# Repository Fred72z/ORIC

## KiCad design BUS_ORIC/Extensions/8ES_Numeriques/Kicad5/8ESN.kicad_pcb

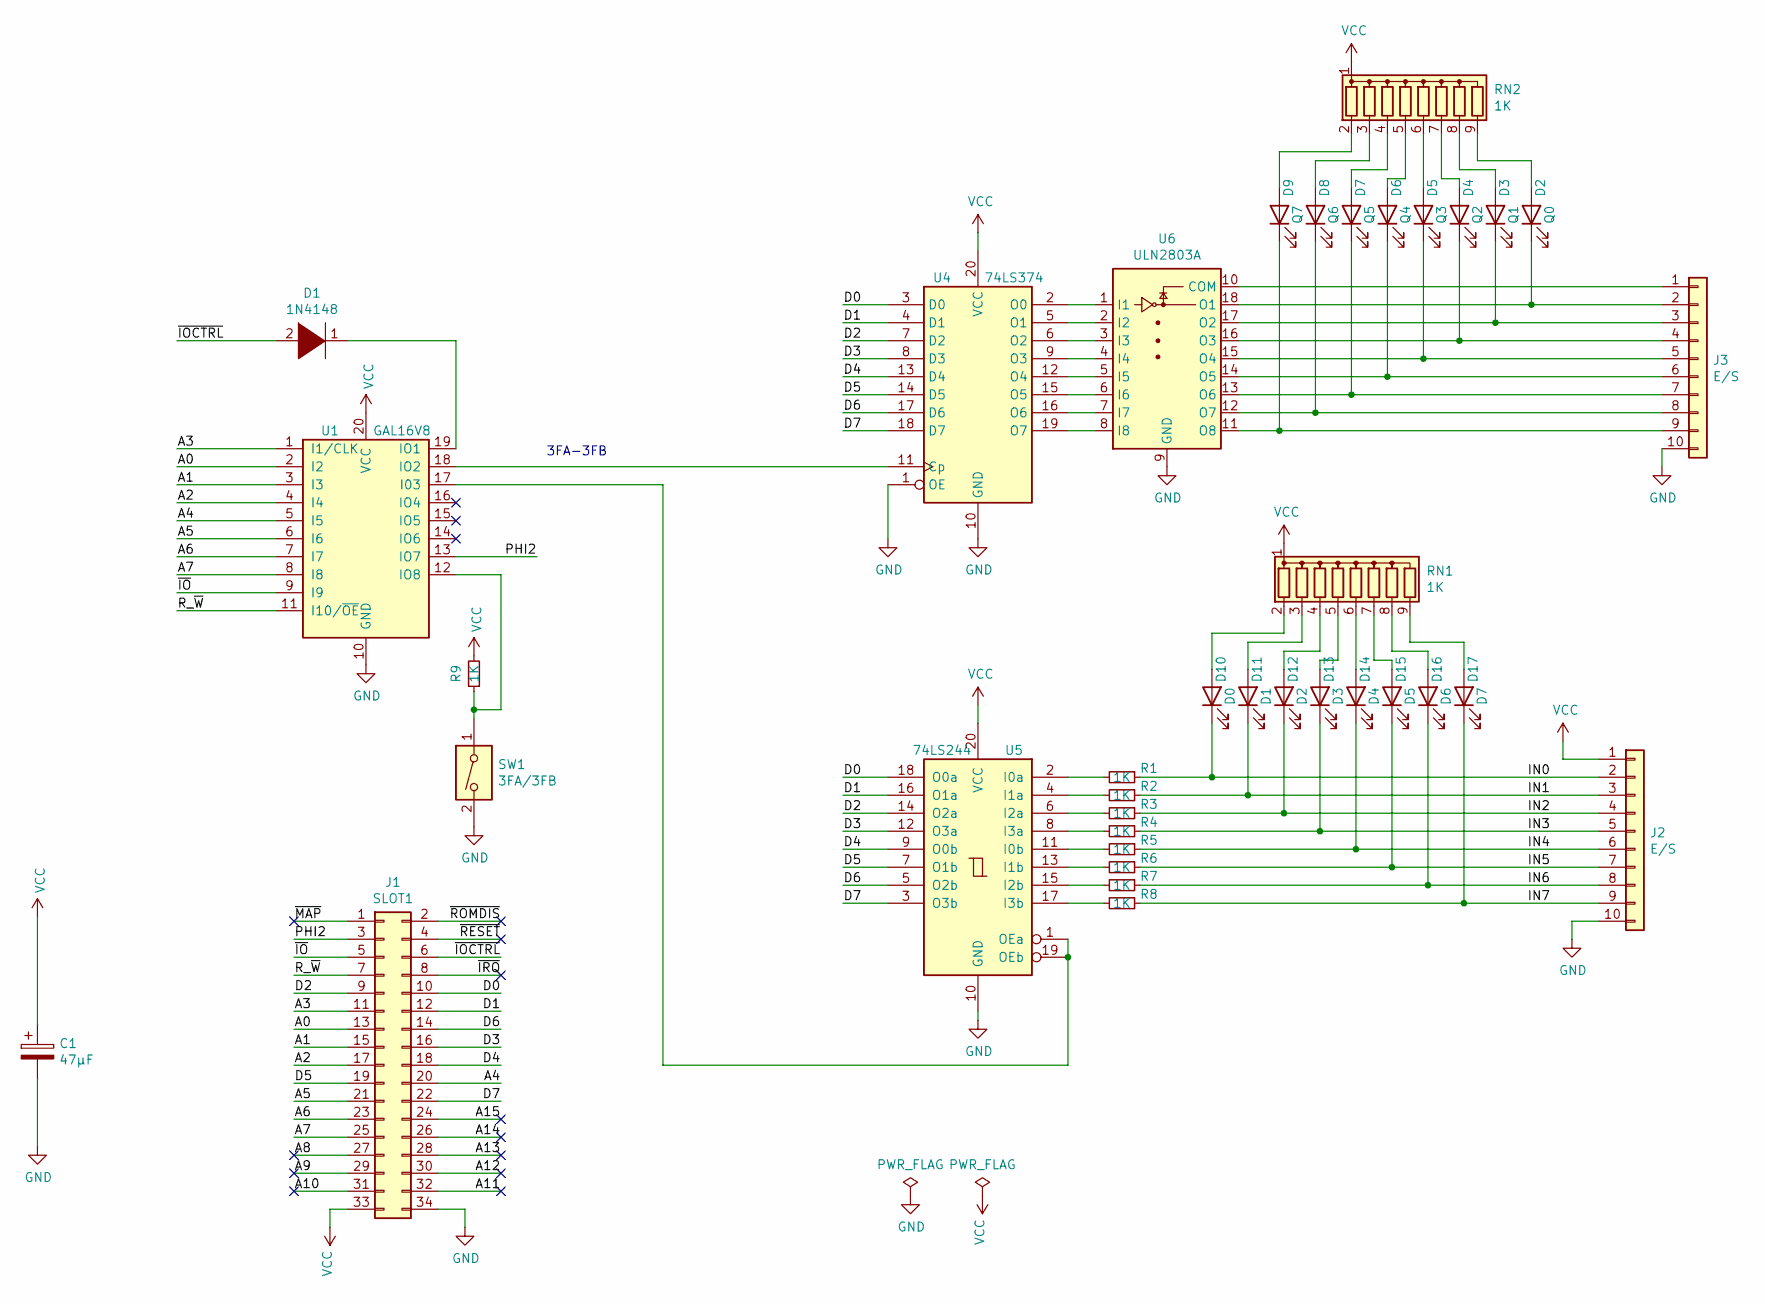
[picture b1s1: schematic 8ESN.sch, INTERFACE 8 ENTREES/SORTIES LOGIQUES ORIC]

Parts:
C1: 47µF; CP_Radial_D5.0mm_P2.00mm
D1: 1N4148; D_DO-35_SOD27_P7.62mm_Horizontal
D2: Q0; LED_0805_2012Metric
D3: Q1; LED_0805_2012Metric
D4: Q2; LED_0805_2012Metric
D5: Q3; LED_0805_2012Metric
D6: Q4; LED_0805_2012Metric
D7: Q5; LED_0805_2012Metric
D8: Q6; LED_0805_2012Metric
D9: Q7; LED_0805_2012Metric
D10: D0; LED_0805_2012Metric
D11: D1; LED_0805_2012Metric
D12: D2; LED_0805_2012Metric
D13: D3; LED_0805_2012Metric
D14: D4; LED_0805_2012Metric
D15: D5; LED_0805_2012Metric
D16: D6; LED_0805_2012Metric
D17: D7; LED_0805_2012Metric
J1: SLOT1; IDC-Header_2x17_P2.54mm_Horizontal
J2, J3: E/S; PinHeader_1x10_P2.54mm_Horizontal
R1, R2, R3, R4, R5, R6, R7, R8: 1K; R_Axial_DIN0204_L3.6mm_D1.6mm_P2.54mm_Vertical
R9: 1K; R_Axial_DIN0204_L3.6mm_D1.6mm_P7.62mm_Horizontal
RN1, RN2: 1K; R_Array_SIP9
SW1: 3FA/3FB; SW_DIP_SPSTx01_Slide_6.7x4.1mm_W7.62mm_P2.54mm_LowProfile
U1: GAL16V8; DIP-20_W7.62mm_LongPads
U4: 74LS374; DIP-20_W7.62mm_LongPads
U5: 74LS244; DIP-20_W7.62mm_LongPads
U6: ULN2803A; DIP-18_W7.62mm_LongPads

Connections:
/A0: J1.13, U1.2 (I2)
/A1: J1.15, U1.3 (I3)
/A2: J1.17, U1.4 (I4)
/A3: J1.11, U1.1 (I1/CLK)
/A4: J1.20, U1.5 (I5)
/A5: J1.21, U1.6 (I6)
/A6: J1.23, U1.7 (I7)
/A7: J1.25, U1.8 (I8)
/A8: J1.27
/A9: J1.29
/A10: J1.31
/A11: J1.32
/A12: J1.30
/A13: J1.28
/A14: J1.26
/A15: J1.24
/D0: J1.10, U4.3 (D0), U5.18 (O0a)
/D1: J1.12, U4.4 (D1), U5.16 (O1a)
/D2: J1.9, U4.7 (D2), U5.14 (O2a)
/D3: J1.16, U4.8 (D3), U5.12 (O3a)
/D4: J1.18, U4.13 (D4), U5.9 (O0b)
/D5: J1.19, U4.14 (D5), U5.7 (O1b)
/D6: J1.14, U4.17 (D6), U5.5 (O2b)
/D7: J1.22, U4.18 (D7), U5.3 (O3b)
/IN0: D10.1 (K), J2.2, R1.1
/IN1: D11.1 (K), J2.3, R2.1
/IN2: D12.1 (K), J2.4, R3.1
/IN3: D13.1 (K), J2.5, R4.1
/IN4: D14.1 (K), J2.6, R5.1
/IN5: D15.1 (K), J2.7, R6.1
/IN6: D16.1 (K), J2.8, R7.1
/IN7: D17.1 (K), J2.9, R8.1
/PHI2: J1.3, U1.13 (IO7)
/R_~W: J1.7, U1.11 (I10/~OE~)
/~IO: J1.5, U1.9 (I9)
/~IOCTRL: D1.2 (A), J1.6
/~IRQ: J1.8
/~MAP: J1.1
/~RESET: J1.4
/~ROMDIS: J1.2
GND: C1.2, J1.34, J2.10, J3.10, SW1.2, U1.10 (GND), U4.1 (OE), U4.10 (GND), U5.10 (GND), U6.9 (GND)
unnamed: D1.1 (K), U1.19 (IO1)
unnamed: D2.1 (K), J3.2, U6.18 (O1)
unnamed: D2.2 (A), RN2.9 (R8)
unnamed: D3.1 (K), J3.3, U6.17 (O2)
unnamed: D3.2 (A), RN2.8 (R7)
unnamed: D4.1 (K), J3.4, U6.16 (O3)
unnamed: D4.2 (A), RN2.7 (R6)
unnamed: D5.1 (K), J3.5, U6.15 (O4)
unnamed: D5.2 (A), RN2.6 (R5)
unnamed: D6.1 (K), J3.6, U6.14 (O5)
unnamed: D6.2 (A), RN2.5 (R4)
unnamed: D7.1 (K), J3.7, U6.13 (O6)
unnamed: D7.2 (A), RN2.4 (R3)
unnamed: D8.1 (K), J3.8, U6.12 (O7)
unnamed: D8.2 (A), RN2.3 (R2)
unnamed: D9.1 (K), J3.9, U6.11 (O8)
unnamed: D9.2 (A), RN2.2 (R1)
unnamed: D10.2 (A), RN1.2 (R1)
unnamed: D11.2 (A), RN1.3 (R2)
unnamed: D12.2 (A), RN1.4 (R3)
unnamed: D13.2 (A), RN1.5 (R4)
unnamed: D14.2 (A), RN1.6 (R5)
unnamed: D15.2 (A), RN1.7 (R6)
unnamed: D16.2 (A), RN1.8 (R7)
unnamed: D17.2 (A), RN1.9 (R8)
unnamed: J3.1, U6.10 (COM)
unnamed: R1.2, U5.2 (I0a)
unnamed: R2.2, U5.4 (I1a)
unnamed: R3.2, U5.6 (I2a)
unnamed: R4.2, U5.8 (I3a)
unnamed: R5.2, U5.11 (I0b)
unnamed: R6.2, U5.13 (I1b)
unnamed: R7.2, U5.15 (I2b)
unnamed: R8.2, U5.17 (I3b)
unnamed: R9.1, SW1.1, U1.12 (IO8)
unnamed: U1.17 (I03), U5.1 (OEa), U5.19 (OEb)
unnamed: U1.18 (IO2), U4.11 (Cp)
unnamed: U4.2 (O0), U6.1 (I1)
unnamed: U4.5 (O1), U6.2 (I2)
unnamed: U4.6 (O2), U6.3 (I3)
unnamed: U4.9 (O3), U6.4 (I4)
unnamed: U4.12 (O4), U6.5 (I5)
unnamed: U4.15 (O5), U6.6 (I6)
unnamed: U4.16 (O6), U6.7 (I7)
unnamed: U4.19 (O7), U6.8 (I8)
VCC: C1.1, J1.33, J2.1, R9.2, RN1.1 (common), RN2.1 (common), U1.20 (VCC), U4.20 (VCC), U5.20 (VCC)

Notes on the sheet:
3FA-3FB

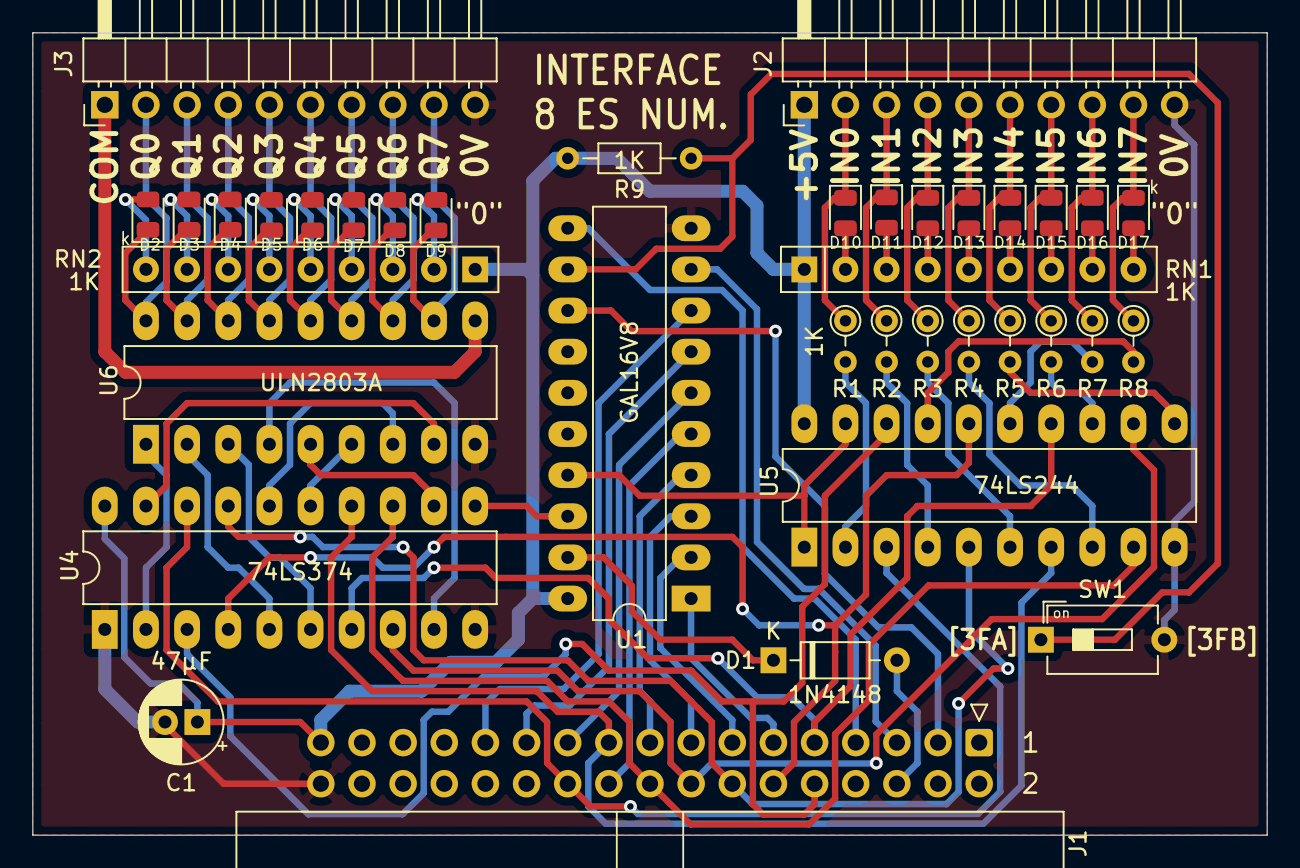
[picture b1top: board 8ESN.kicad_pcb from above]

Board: 2 copper layers, 76.2 x 49.5 mm, 37 parts (0 on the bottom side), 75 nets.

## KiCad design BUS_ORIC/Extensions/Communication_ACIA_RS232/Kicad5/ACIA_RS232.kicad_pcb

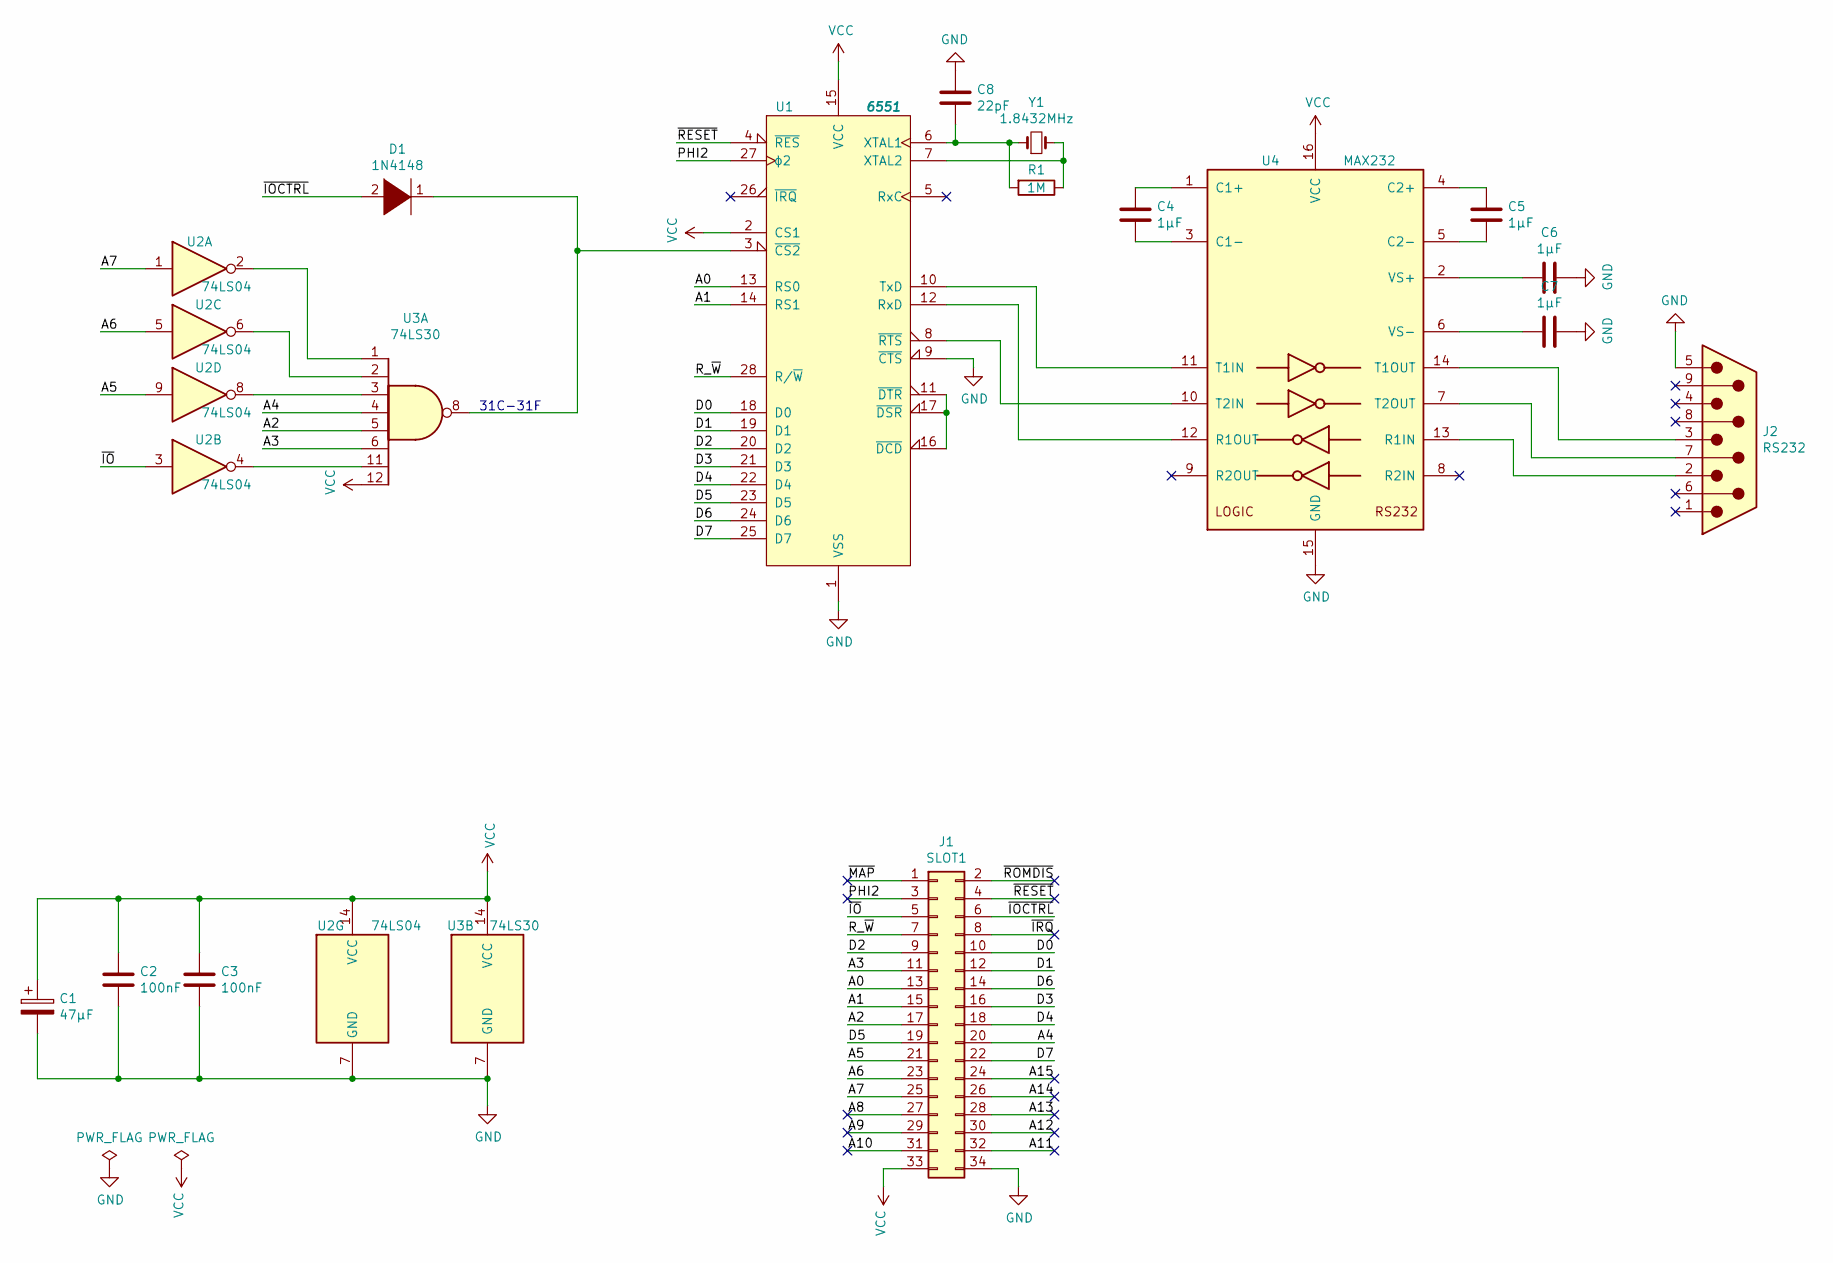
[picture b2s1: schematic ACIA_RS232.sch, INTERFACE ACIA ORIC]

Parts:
C1: 47µF; CP_Radial_D5.0mm_P2.00mm
C2, C3: 100nF; C_Rect_L7.0mm_W2.0mm_P5.00mm
C4, C5, C6, C7: 1µF; CP_Radial_D5.0mm_P2.00mm
C8: 22pF; C_Disc_D3.4mm_W2.1mm_P2.50mm
D1: 1N4148; D_DO-35_SOD27_P7.62mm_Horizontal
J1: SLOT1; IDC-Header_2x17_P2.54mm_Horizontal
J2: RS232; DSUB-9_Male_Horizontal_P2.77x2.84mm
R1: 1M; R_Axial_DIN0207_L6.3mm_D2.5mm_P10.16mm_Horizontal
U1: 6551; DIP-28_W15.24mm_LongPads
U2: 74LS04; DIP-14_W7.62mm_LongPads
U3: 74LS30; DIP-14_W7.62mm_LongPads
U4: MAX232; DIP-16_W7.62mm_LongPads
Y1: 1.8432MHz; Crystal_HC49-U_Horizontal

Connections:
/A0: J1.13, U1.13 (RS0)
/A1: J1.15, U1.14 (RS1)
/A2: J1.17, U3.5
/A3: J1.11, U3.6
/A4: J1.20, U3.4
/A5: J1.21, U2.9
/A6: J1.23, U2.5
/A7: J1.25, U2.1
/A8: J1.27
/A9: J1.29
/A10: J1.31
/A11: J1.32
/A12: J1.30
/A13: J1.28
/A14: J1.26
/A15: J1.24
/D0: J1.10, U1.18 (D0)
/D1: J1.12, U1.19 (D1)
/D2: J1.9, U1.20 (D2)
/D3: J1.16, U1.21 (D3)
/D4: J1.18, U1.22 (D4)
/D5: J1.19, U1.23 (D5)
/D6: J1.14, U1.24 (D6)
/D7: J1.22, U1.25 (D7)
/PHI2: J1.3, U1.27 (ϕ2)
/R_~W: J1.7, U1.28 (R/~W)
/~IO: J1.5, U2.3
/~IOCTRL: D1.2 (A), J1.6
/~IRQ: J1.8
/~MAP: J1.1
/~RESET: J1.4, U1.4 (~RES)
/~ROMDIS: J1.2
GND: C1.2, C2.1, C3.1, C6.1, C7.1, C8.1, J1.34, J2.5, U1.1 (VSS), U1.9 (~CTS), U2.7 (GND), U3.7 (GND), U4.15 (GND)
unnamed: C4.1, U4.1 (C1+)
unnamed: C4.2, U4.3 (C1-)
unnamed: C5.1, U4.4 (C2+)
unnamed: C5.2, U4.5 (C2-)
unnamed: C6.2, U4.2 (VS+)
unnamed: C7.2, U4.6 (VS-)
unnamed: C8.2, R1.2, U1.6 (XTAL1), Y1.1
unnamed: D1.1 (K), U1.3 (~CS2), U3.8
unnamed: J2.2, U4.13 (R1IN)
unnamed: J2.3, U4.14 (T1OUT)
unnamed: J2.7, U4.7 (T2OUT)
unnamed: R1.1, U1.7 (XTAL2), Y1.2
unnamed: U1.8 (~RTS), U4.10 (T2IN)
unnamed: U1.10 (TxD), U4.11 (T1IN)
unnamed: U1.11 (~DTR), U1.16 (~DCD), U1.17 (~DSR)
unnamed: U1.12 (RxD), U4.12 (R1OUT)
unnamed: U2.2, U3.1
unnamed: U2.4, U3.11
unnamed: U2.6, U3.2
unnamed: U2.8, U3.3
VCC: C1.1, C2.2, C3.2, J1.33, U1.2 (CS1), U1.15 (VCC), U2.14 (VCC), U3.12, U3.14 (VCC), U4.16 (VCC)

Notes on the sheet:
31C-31F

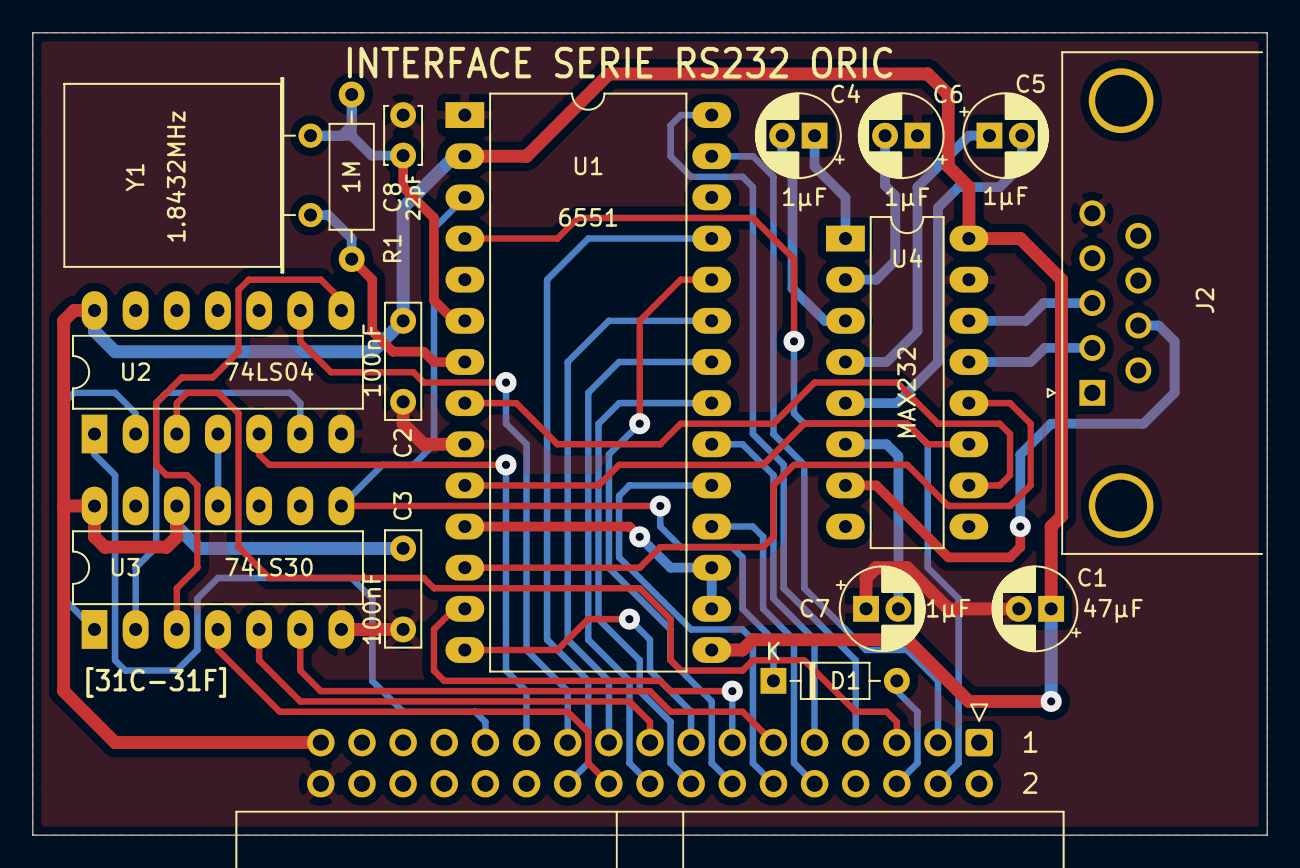
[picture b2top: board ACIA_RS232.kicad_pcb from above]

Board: 2 copper layers, 76.2 x 49.5 mm, 17 parts (0 on the bottom side), 43 nets.

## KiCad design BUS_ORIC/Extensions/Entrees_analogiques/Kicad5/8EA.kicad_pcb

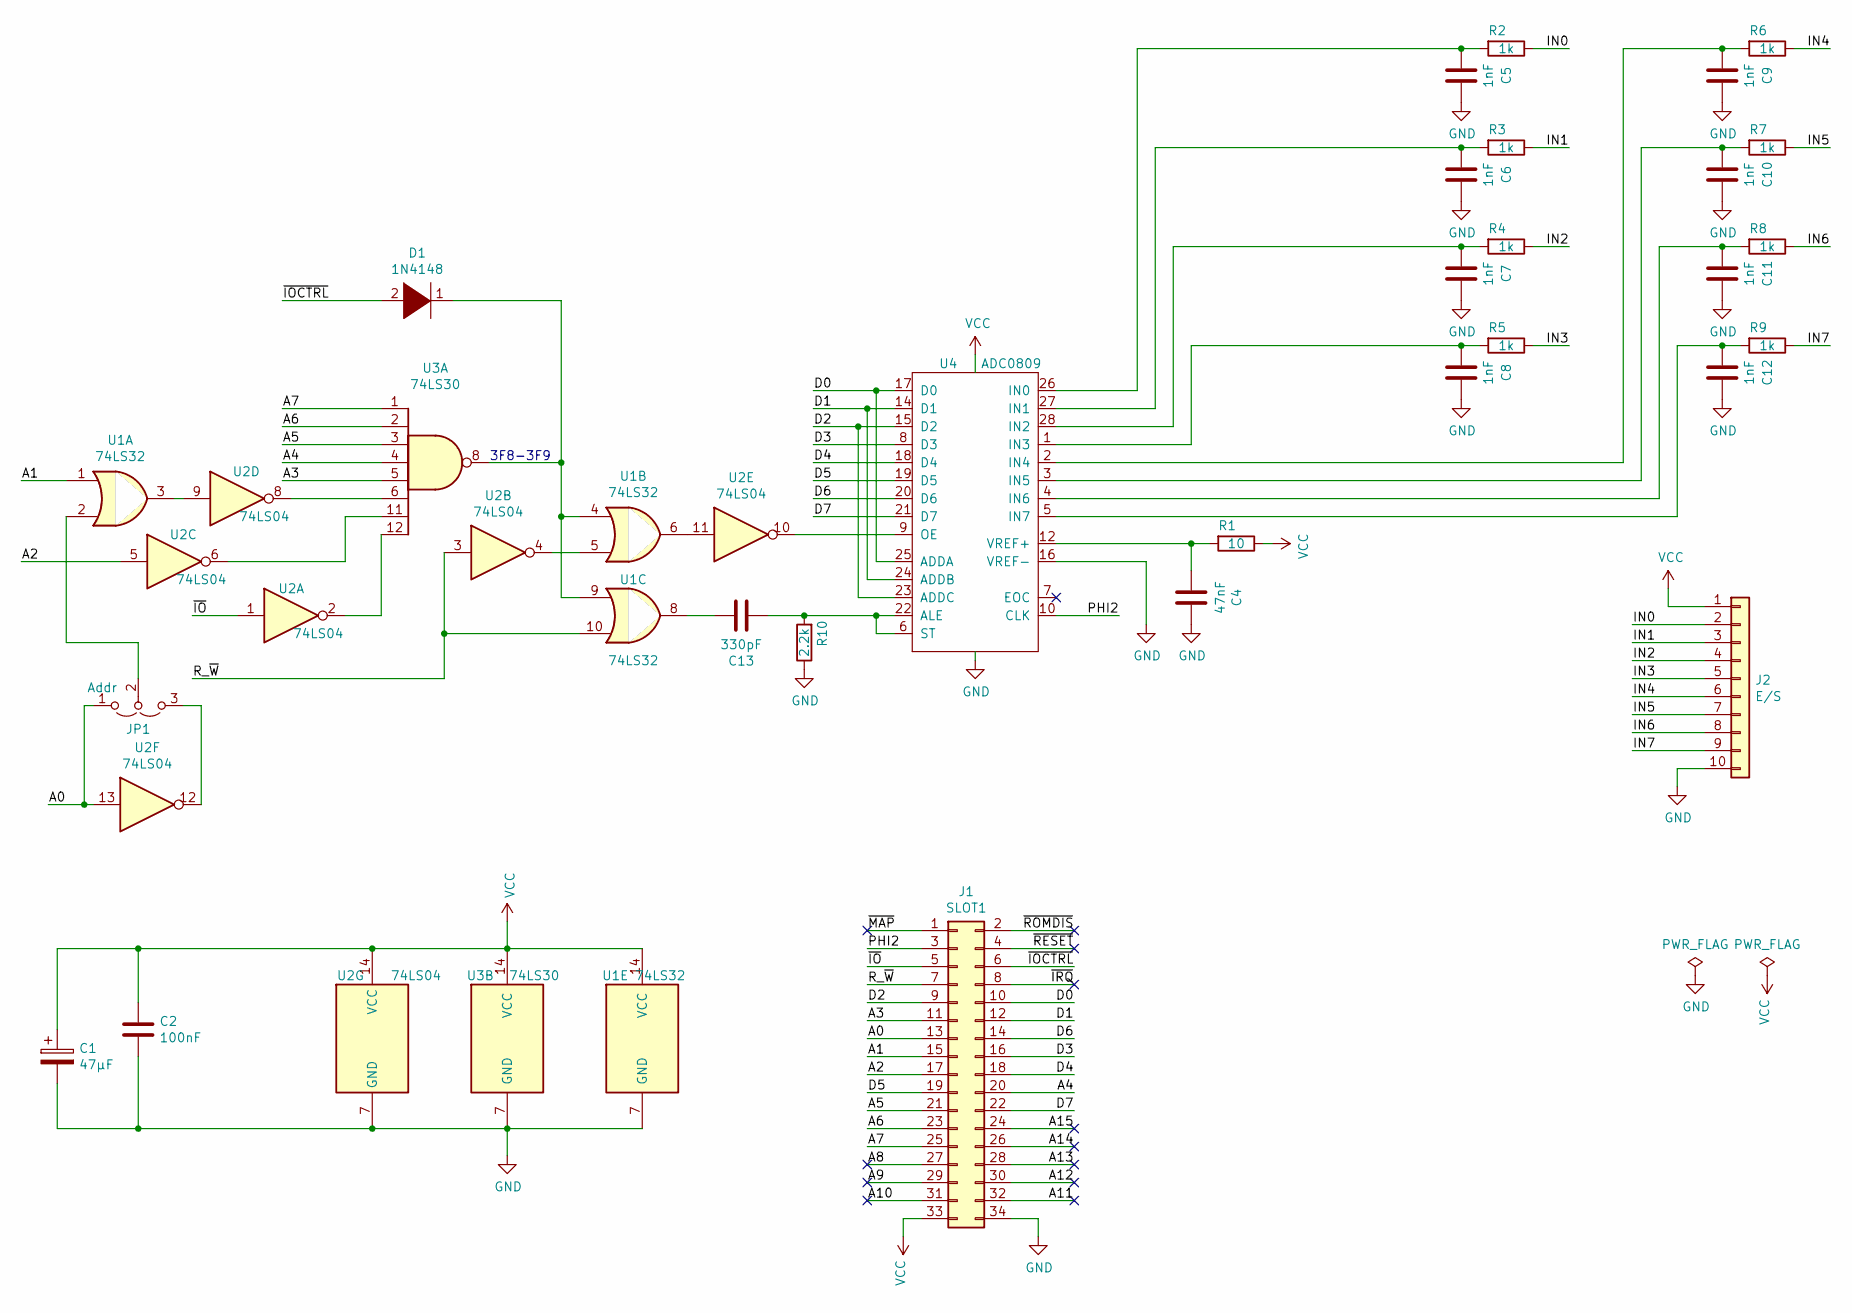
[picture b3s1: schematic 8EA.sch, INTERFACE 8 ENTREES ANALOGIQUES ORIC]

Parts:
C1: 47µF; CP_Radial_D5.0mm_P2.00mm
C2: 100nF; C_Rect_L7.0mm_W2.0mm_P5.00mm
C4: 47nF; C_Rect_L7.0mm_W2.0mm_P5.00mm
C5, C6, C7, C8, C9, C10, C11, C12: 1nF; C_Rect_L7.0mm_W2.0mm_P5.00mm
C13: 330pF; C_Disc_D3.4mm_W2.1mm_P2.50mm
D1: 1N4148; D_DO-35_SOD27_P7.62mm_Horizontal
J1: SLOT1; IDC-Header_2x17_P2.54mm_Horizontal
J2: E/S; PinHeader_1x10_P2.54mm_Horizontal
JP1: Addr; PinHeader_1x03_P2.54mm_Vertical
R1: 10; R_Axial_DIN0207_L6.3mm_D2.5mm_P10.16mm_Horizontal
R2, R3, R4, R5, R6, R7, R8, R9: 1k; R_Axial_DIN0207_L6.3mm_D2.5mm_P10.16mm_Horizontal
R10: 2.2k; R_Axial_DIN0207_L6.3mm_D2.5mm_P10.16mm_Horizontal
U1: 74LS32; DIP-14_W7.62mm_LongPads
U2: 74LS04; DIP-14_W7.62mm_LongPads
U3: 74LS30; DIP-14_W7.62mm_LongPads
U4: ADC0809; DIP-28_W15.24mm_LongPads

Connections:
/A0: J1.13, JP1.1 (A), U2.13
/A1: J1.15, U1.1
/A2: J1.17, U2.5
/A3: J1.11, U3.5
/A4: J1.20, U3.4
/A5: J1.21, U3.3
/A6: J1.23, U3.2
/A7: J1.25, U3.1
/A8: J1.27
/A9: J1.29
/A10: J1.31
/A11: J1.32
/A12: J1.30
/A13: J1.28
/A14: J1.26
/A15: J1.24
/D0: J1.10, U4.17 (D0), U4.25 (ADDA)
/D1: J1.12, U4.14 (D1), U4.24 (ADDB)
/D2: J1.9, U4.15 (D2), U4.23 (ADDC)
/D3: J1.16, U4.8 (D3)
/D4: J1.18, U4.18 (D4)
/D5: J1.19, U4.19 (D5)
/D6: J1.14, U4.20 (D6)
/D7: J1.22, U4.21 (D7)
/IN0: J2.2, R2.1
/IN1: J2.3, R3.1
/IN2: J2.4, R4.1
/IN3: J2.5, R5.1
/IN4: J2.6, R6.1
/IN5: J2.7, R7.1
/IN6: J2.8, R8.1
/IN7: J2.9, R9.1
/PHI2: J1.3, U4.10 (CLK)
/R_~W: J1.7, U1.10, U2.3
/~IO: J1.5, U2.1
/~IOCTRL: D1.2 (A), J1.6
/~IRQ: J1.8
/~MAP: J1.1
/~RESET: J1.4
/~ROMDIS: J1.2
GND: C1.2, C2.1, C4.1, C5.1, C6.1, C7.1, C8.1, C9.1, C10.1, C11.1, C12.1, J1.34, J2.10, R10.1, U1.7 (GND), U2.7 (GND), U3.7 (GND), U4.13 (GND), U4.16 (VREF-)
unnamed: C4.2, R1.2, U4.12 (VREF+)
unnamed: C5.2, R2.2, U4.26 (IN0)
unnamed: C6.2, R3.2, U4.27 (IN1)
unnamed: C7.2, R4.2, U4.28 (IN2)
unnamed: C8.2, R5.2, U4.1 (IN3)
unnamed: C9.2, R6.2, U4.2 (IN4)
unnamed: C10.2, R7.2, U4.3 (IN5)
unnamed: C11.2, R8.2, U4.4 (IN6)
unnamed: C12.2, R9.2, U4.5 (IN7)
unnamed: C13.1, U1.8
unnamed: C13.2, R10.2, U4.6 (ST), U4.22 (ALE)
unnamed: D1.1 (K), U1.4, U1.9, U3.8
unnamed: JP1.2 (C), U1.2
unnamed: JP1.3 (B), U2.12
unnamed: U1.3, U2.9
unnamed: U1.5, U2.4
unnamed: U1.6, U2.11
unnamed: U2.2, U3.12
unnamed: U2.6, U3.11
unnamed: U2.8, U3.6
unnamed: U2.10, U4.9 (OE)
VCC: C1.1, C2.2, J1.33, J2.1, R1.1, U1.14 (VCC), U2.14 (VCC), U3.14 (VCC), U4.11 (VCC)

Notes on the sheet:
3F8-3F9

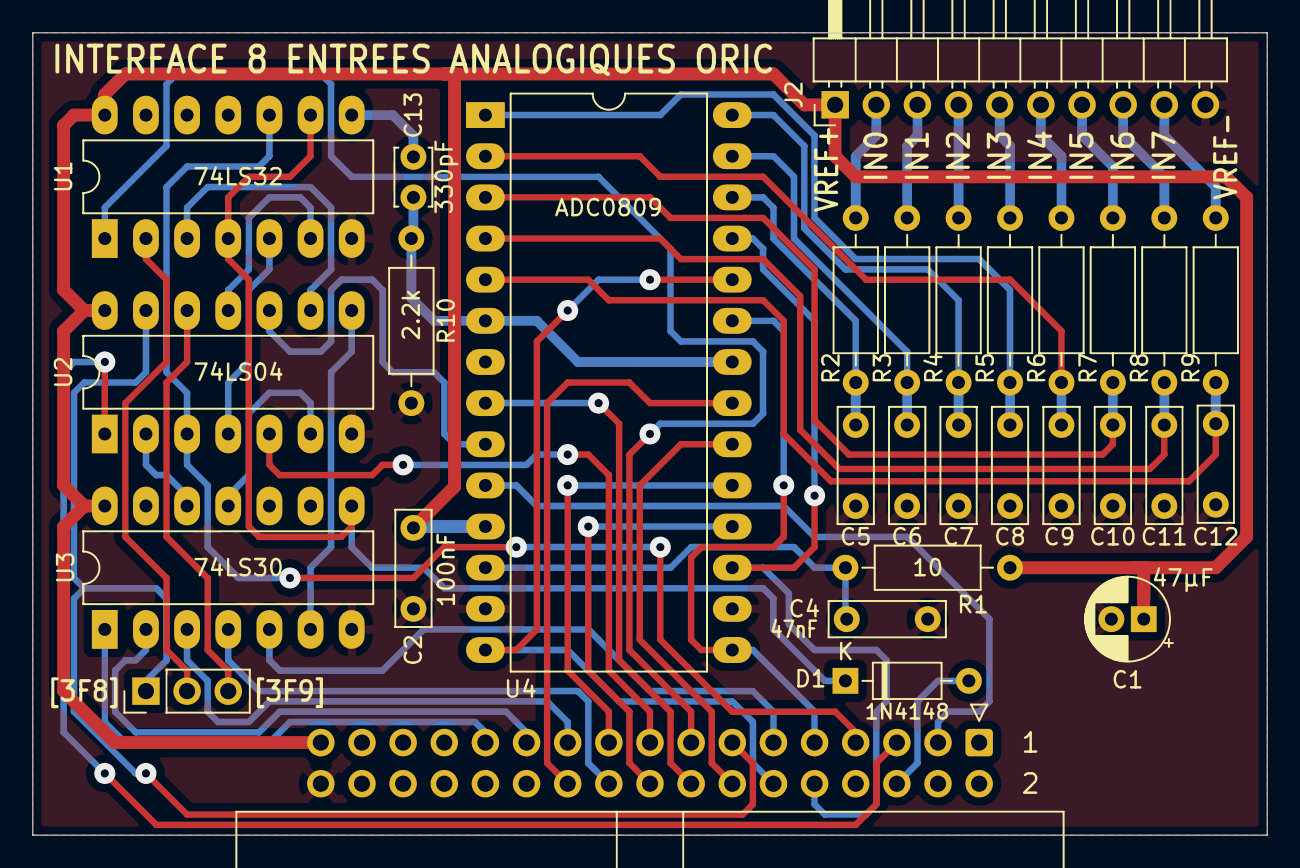
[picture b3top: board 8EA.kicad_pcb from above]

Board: 2 copper layers, 76.2 x 49.5 mm, 30 parts (0 on the bottom side), 51 nets.

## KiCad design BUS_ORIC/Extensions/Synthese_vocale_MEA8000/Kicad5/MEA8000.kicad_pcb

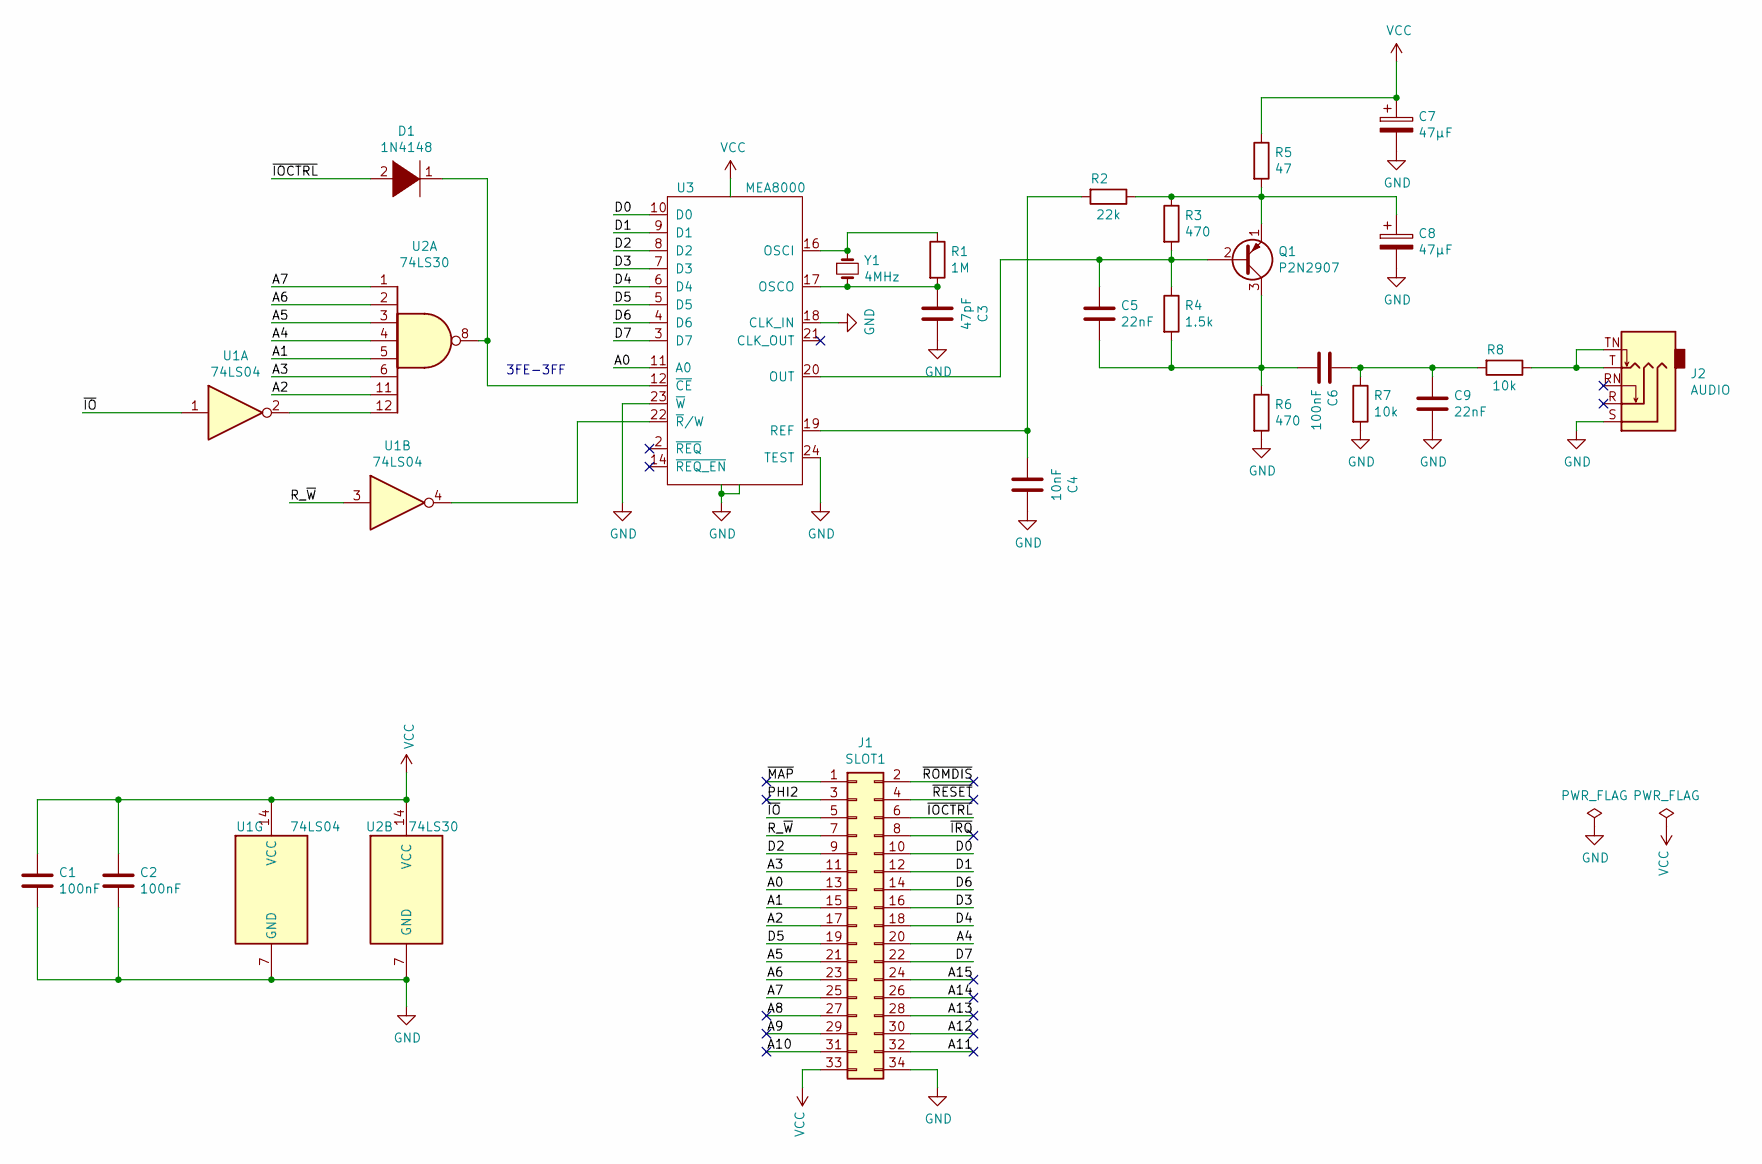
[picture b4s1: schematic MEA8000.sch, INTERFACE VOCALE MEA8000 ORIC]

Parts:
C1, C2, C6: 100nF; C_Rect_L7.0mm_W2.0mm_P5.00mm
C3: 47pF; C_Rect_L7.0mm_W2.0mm_P5.00mm
C4: 10nF; C_Rect_L7.0mm_W2.0mm_P5.00mm
C5, C9: 22nF; C_Rect_L7.0mm_W2.0mm_P5.00mm
C7, C8: 47µF; CP_Radial_D5.0mm_P2.00mm
D1: 1N4148; D_DO-35_SOD27_P7.62mm_Horizontal
J1: SLOT1; IDC-Header_2x17_P2.54mm_Horizontal
J2: AUDIO; Jack_3.5mm_PJ-307_Horizontal
Q1: P2N2907; TO-92
R1: 1M; R_Axial_DIN0207_L6.3mm_D2.5mm_P10.16mm_Horizontal
R2: 22k; R_Axial_DIN0207_L6.3mm_D2.5mm_P10.16mm_Horizontal
R3, R6: 470; R_Axial_DIN0207_L6.3mm_D2.5mm_P10.16mm_Horizontal
R4: 1.5k; R_Axial_DIN0207_L6.3mm_D2.5mm_P10.16mm_Horizontal
R5: 47; R_Axial_DIN0207_L6.3mm_D2.5mm_P10.16mm_Horizontal
R7, R8: 10k; R_Axial_DIN0207_L6.3mm_D2.5mm_P10.16mm_Horizontal
U1: 74LS04; DIP-14_W7.62mm_LongPads
U2: 74LS30; DIP-14_W7.62mm_LongPads
U3: MEA8000; DIP-24_W15.24mm_LongPads
Y1: 4MHz; Crystal_HC49-U_Vertical

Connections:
/A0: J1.13, U3.11 (A0)
/A1: J1.15, U2.5
/A2: J1.17, U2.11
/A3: J1.11, U2.6
/A4: J1.20, U2.4
/A5: J1.21, U2.3
/A6: J1.23, U2.2
/A7: J1.25, U2.1
/A8: J1.27
/A9: J1.29
/A10: J1.31
/A11: J1.32
/A12: J1.30
/A13: J1.28
/A14: J1.26
/A15: J1.24
/D0: J1.10, U3.10 (D0)
/D1: J1.12, U3.9 (D1)
/D2: J1.9, U3.8 (D2)
/D3: J1.16, U3.7 (D3)
/D4: J1.18, U3.6 (D4)
/D5: J1.19, U3.5 (D5)
/D6: J1.14, U3.4 (D6)
/D7: J1.22, U3.3 (D7)
/PHI2: J1.3
/R_~W: J1.7, U1.3
/~IO: J1.5, U1.1
/~IOCTRL: D1.2 (A), J1.6
/~IRQ: J1.8
/~MAP: J1.1
/~RESET: J1.4
/~ROMDIS: J1.2
GND: C1.1, C2.1, C3.1, C4.1, C7.2, C8.2, C9.1, J1.34, J2.S, R6.2, R7.2, U1.7 (GND), U2.7 (GND), U3.1 (VSS), U3.15 (VBB), U3.18 (CLK_IN), U3.23 (~W), U3.24 (TEST)
unnamed: C3.2, R1.2, U3.17 (OSCO), Y1.2
unnamed: C4.2, R2.2, U3.19 (REF)
unnamed: C5.1, C6.1, Q1.3 (C), R4.2, R6.1
unnamed: C5.2, Q1.2 (B), R3.2, R4.1, U3.20 (OUT)
unnamed: C6.2, C9.2, R7.1, R8.2
unnamed: C8.1, Q1.1 (E), R2.1, R3.1, R5.2
unnamed: D1.1 (K), U2.8, U3.12 (~CE)
unnamed: J2.T, J2.TN, R8.1
unnamed: R1.1, U3.16 (OSCI), Y1.1
unnamed: U1.2, U2.12
unnamed: U1.4, U3.22 (~R~/W)
VCC: C1.2, C2.2, C7.1, J1.33, R5.1, U1.14 (VCC), U2.14 (VCC), U3.13 (VDD)

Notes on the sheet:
3FE-3FF

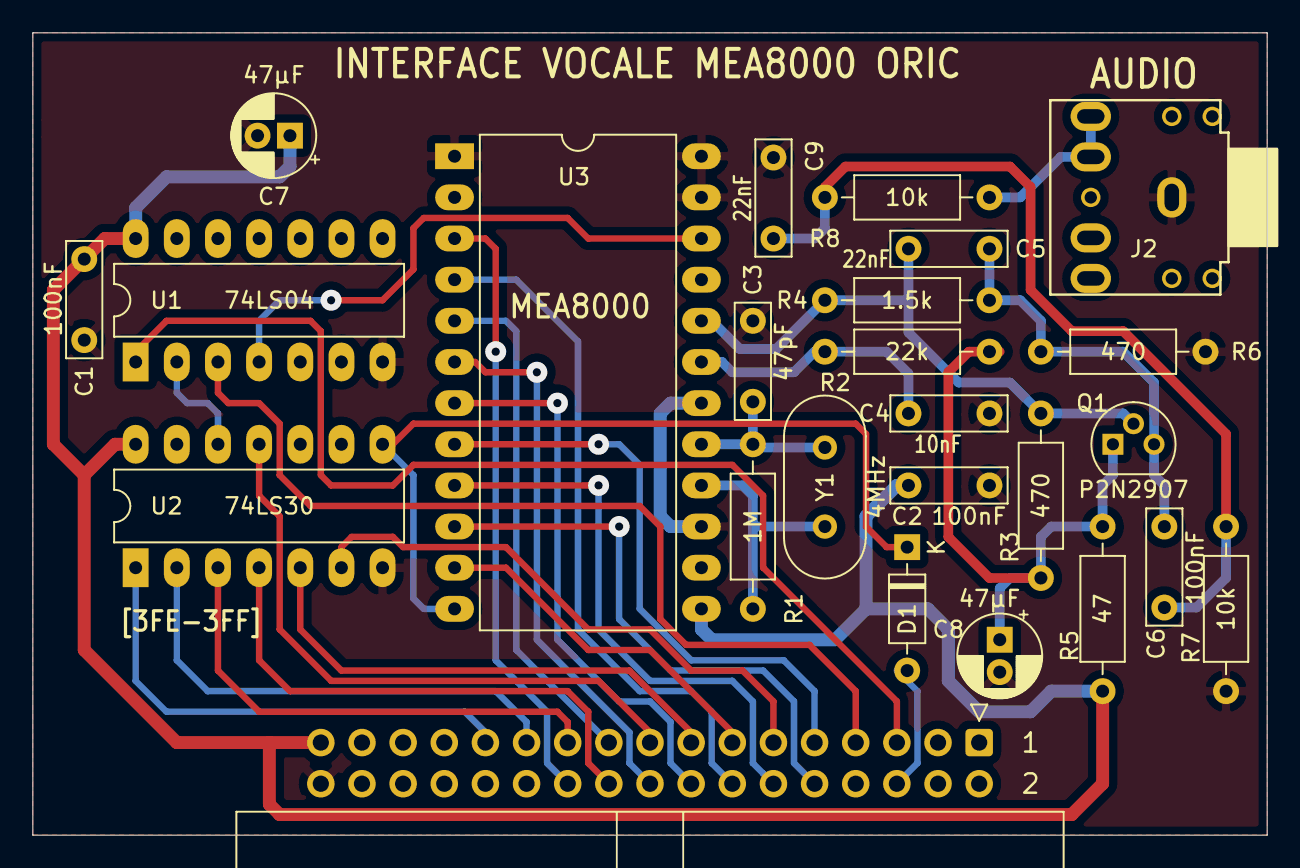
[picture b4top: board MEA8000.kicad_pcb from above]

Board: 2 copper layers, 76.2 x 49.5 mm, 25 parts (0 on the bottom side), 32 nets.
